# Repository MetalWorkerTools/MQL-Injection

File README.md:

# MQL-Injection
A Minimum Quantity Lubrication system based on a car fuel injector and a garden sprayer without the need for compressed air.  

For more information watch this [Video](https://www.youtube.com/watch?v=ADPWYeUzn9Y) and read the [WiKi](https://github.com/MetalWorkerTools/MQL-Injection/wiki).

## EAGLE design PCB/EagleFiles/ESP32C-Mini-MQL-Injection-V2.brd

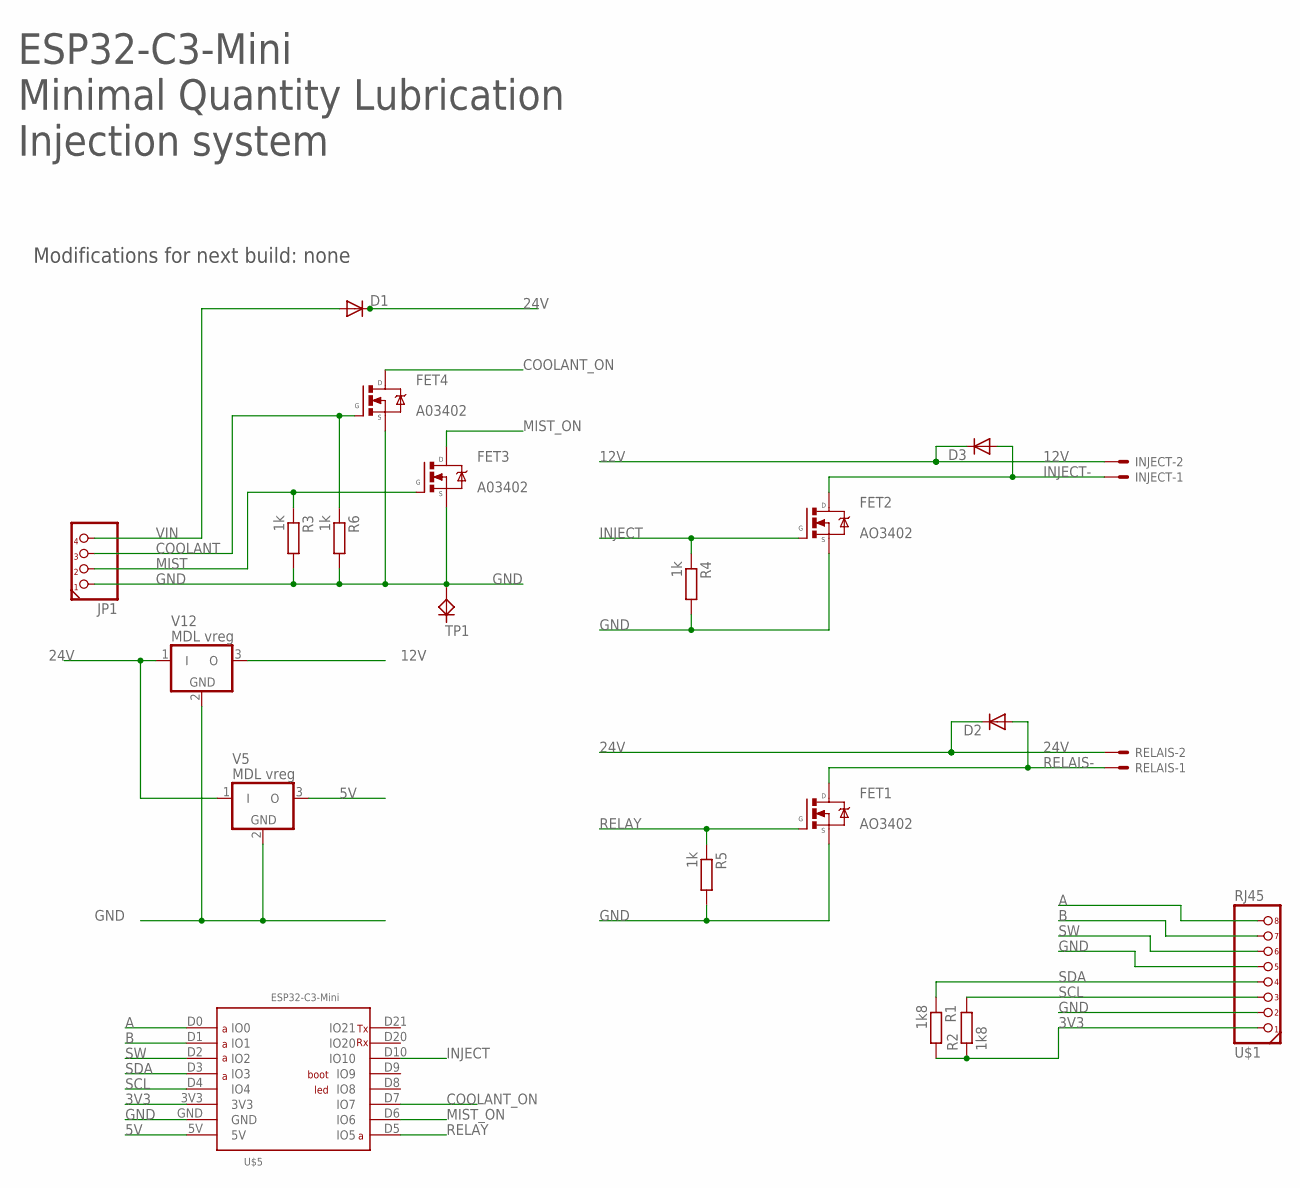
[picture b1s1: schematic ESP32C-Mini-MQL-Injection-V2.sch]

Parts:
D1, D2, D3: DIODE-DO214ACI; DO214ACI
FET1, FET2: AO3402; SOT23-FET
FET3, FET4: A03402; SOT23-FET
INJECT: JST-XH-02-PIN-L; JST-XH-02-L
JP1: PINHD-1X4PH254; 1X04/PH254
R1, R2: 1k8; R0805
R3, R4, R5, R6: 1k; R0805
RELAIS: JST-XH-02-PIN-L; JST-XH-02-L
TP1: TESTPIN-TP10; TP10
U$1: RJ45
U$5: ESP32C3MINIL; ESP32-C3-MINI
V5, V12: MDL vreg; MDLSTEPDOWNV02

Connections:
3V3: R1.2, R2.1, U$1.P$1 (1), U$5.3V3
5V: U$5.5V, V5.3 (O)
12V: D3.C, INJECT.2, V12.3 (O)
24V: D1.C, D2.C, RELAIS.2, V5.1 (I), V12.1 (I)
A: U$1.P$8 (8), U$5.D0 (IO0)
B: U$1.P$7 (7), U$5.D1 (IO1)
COOLANT: FET4.G, JP1.3, R6.1
COOLANT_ON: FET4.D, U$5.D7 (IO7)
GND: FET1.S, FET2.S, FET3.S, FET4.S, JP1.1, R3.2, R4.2, R5.2, R6.2, TP1.TP, U$1.P$2 (2), U$1.P$5 (5), U$5.GND, V5.2 (GND), V12.2 (GND)
INJECT: FET2.G, R4.1, U$5.D10 (IO10)
INJECT-: D3.A, FET2.D, INJECT.1
MIST: FET3.G, JP1.2, R3.1
MIST_ON: FET3.D, U$5.D6 (IO6)
RELAIS-: D2.A, FET1.D, RELAIS.1
RELAY: FET1.G, R5.1, U$5.D5 (IO5)
SCL: R2.2, U$1.P$3 (3), U$5.D4 (IO4)
SDA: R1.1, U$1.P$4 (4), U$5.D3 (IO3)
SW: U$1.P$6 (6), U$5.D2 (IO2)
VIN: D1.A, JP1.4

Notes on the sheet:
ESP32-C3-Mini Minimal Quantity Lubrication Injection system
Modifications for next build: none

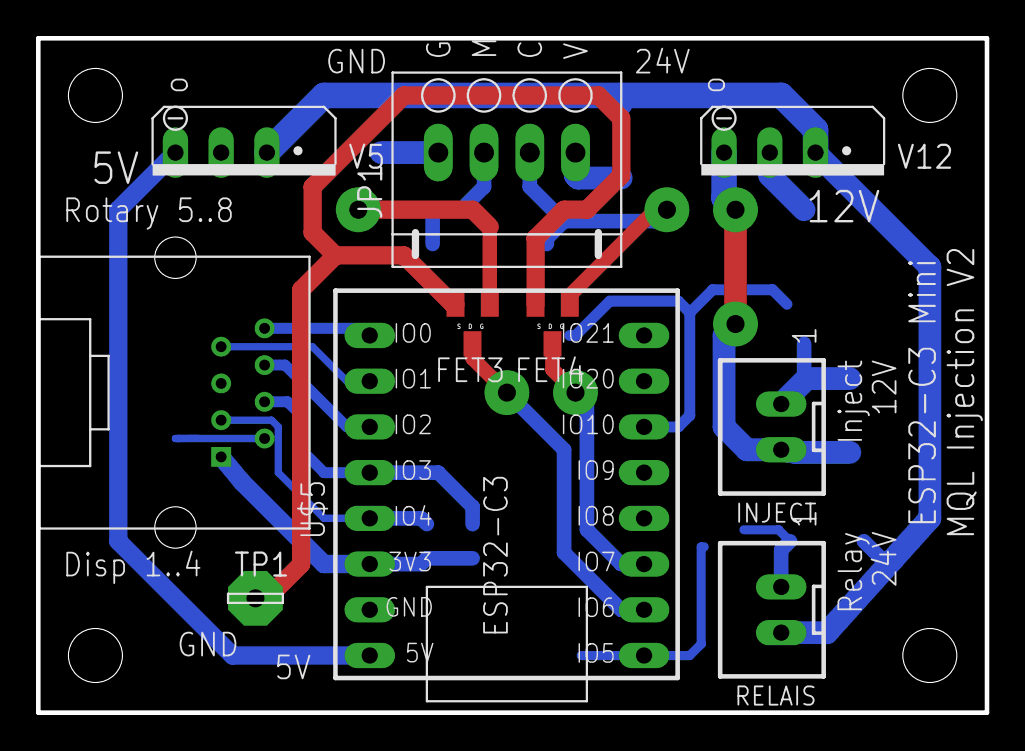
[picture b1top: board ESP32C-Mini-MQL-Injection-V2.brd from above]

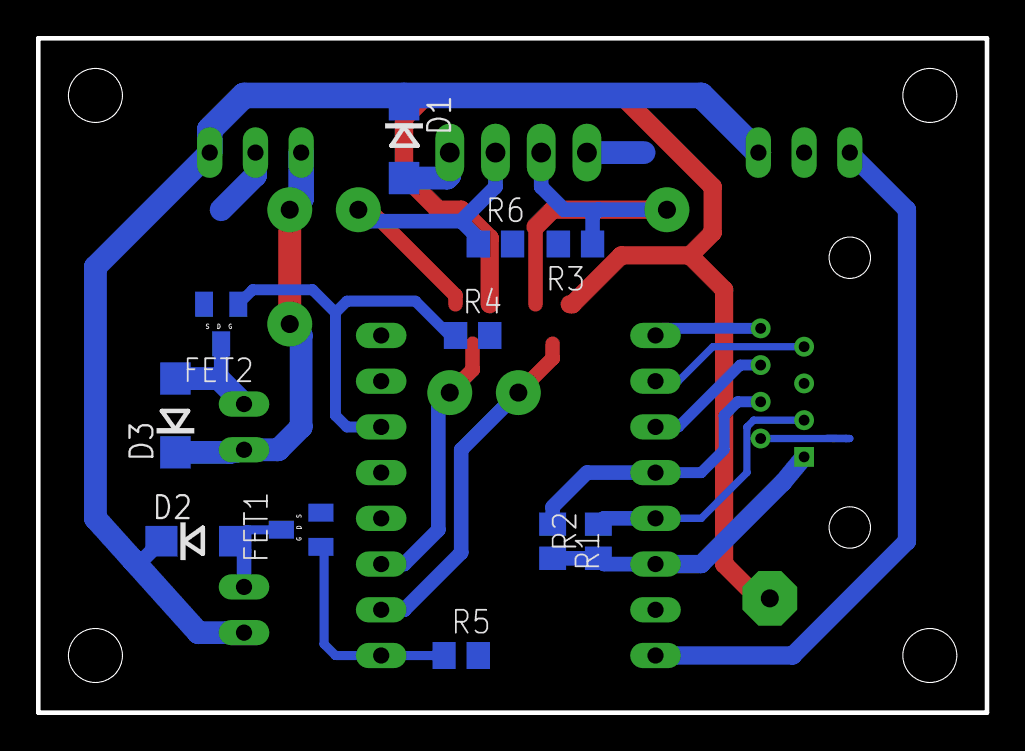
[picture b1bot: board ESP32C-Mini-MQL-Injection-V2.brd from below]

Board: 2 copper layers, 52.7 x 37.5 mm, 21 parts (11 on the bottom side), 19 nets.

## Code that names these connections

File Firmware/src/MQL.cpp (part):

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clsPin PinRotaryA(ROTARY_A_GPIO, INPUT_PULLUP, ROTARY_ACTIVE, false, "A", "a");
clsPin PinRotaryB(ROTARY_B_GPIO, INPUT_PULLUP, ROTARY_ACTIVE, false, "B", "b");
clsPin PinRotarySW(ROTARY_SW_GPIO, INPUT_PULLUP, ROTARY_ACTIVE, false, "S", "s", ROTARY_PRESS_SHORT_TIME);
clsPin PinMist(MIST_GPIO, INPUT_PULLUP, MIST_ACTIVE, false, "M", "m");
clsPin PinCoolant(COOLANT_GPIO, INPUT_PULLUP, COOLANT_ACTIVE, false, "C", "c");
clsPin PinInjection(INJECTION_GPIO, OUTPUT, INJECTION_ACTIVE, false, "I", "i");
clsPin PinRelay(RELAY_GPIO, OUTPUT, RELAY_ACTIVE, false, "R", "r");

bool InjectionActive()
{
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    {
    case ManualModeCoolant:
      SetInjectionActive(false); // Disable injection
      PinRelay.TogglePin();      // Toggle the relay pin
      break;
    case ManualModeMist:
      SetInjectionActive(!InjectionActive());
      PinRelay.SetState(InjectionActive()); // Set the relay state equal to the injection state
      break;
    case ManualModeInjection:
      SetInjectionActive(!InjectionActive());
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
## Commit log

2024-11-11 Added PCB holder step file
2024-11-11 Added Eagle PCB designs and Holder for the board.
2024-11-12 Added the case, changed folder name
2024-11-12 Added Injection system and case
2024-11-12 Updated injection system mount
2024-11-16 Added Firmware release 1.0
2024-11-22 Release 1.1
2025-04-14 Release 1.2
    Reduced the i2c speed to enable longer display wires
2025-04-16 Updated traces
2026-01-24 Fixed typo in README.md
2026-05-04 Added a display reset timer for noisy environments
